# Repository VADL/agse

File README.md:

# agse
Autonomous Ground Support Equipment (AGSE) robot for the Vanderbilt Aerospace Design Lab (VADL)

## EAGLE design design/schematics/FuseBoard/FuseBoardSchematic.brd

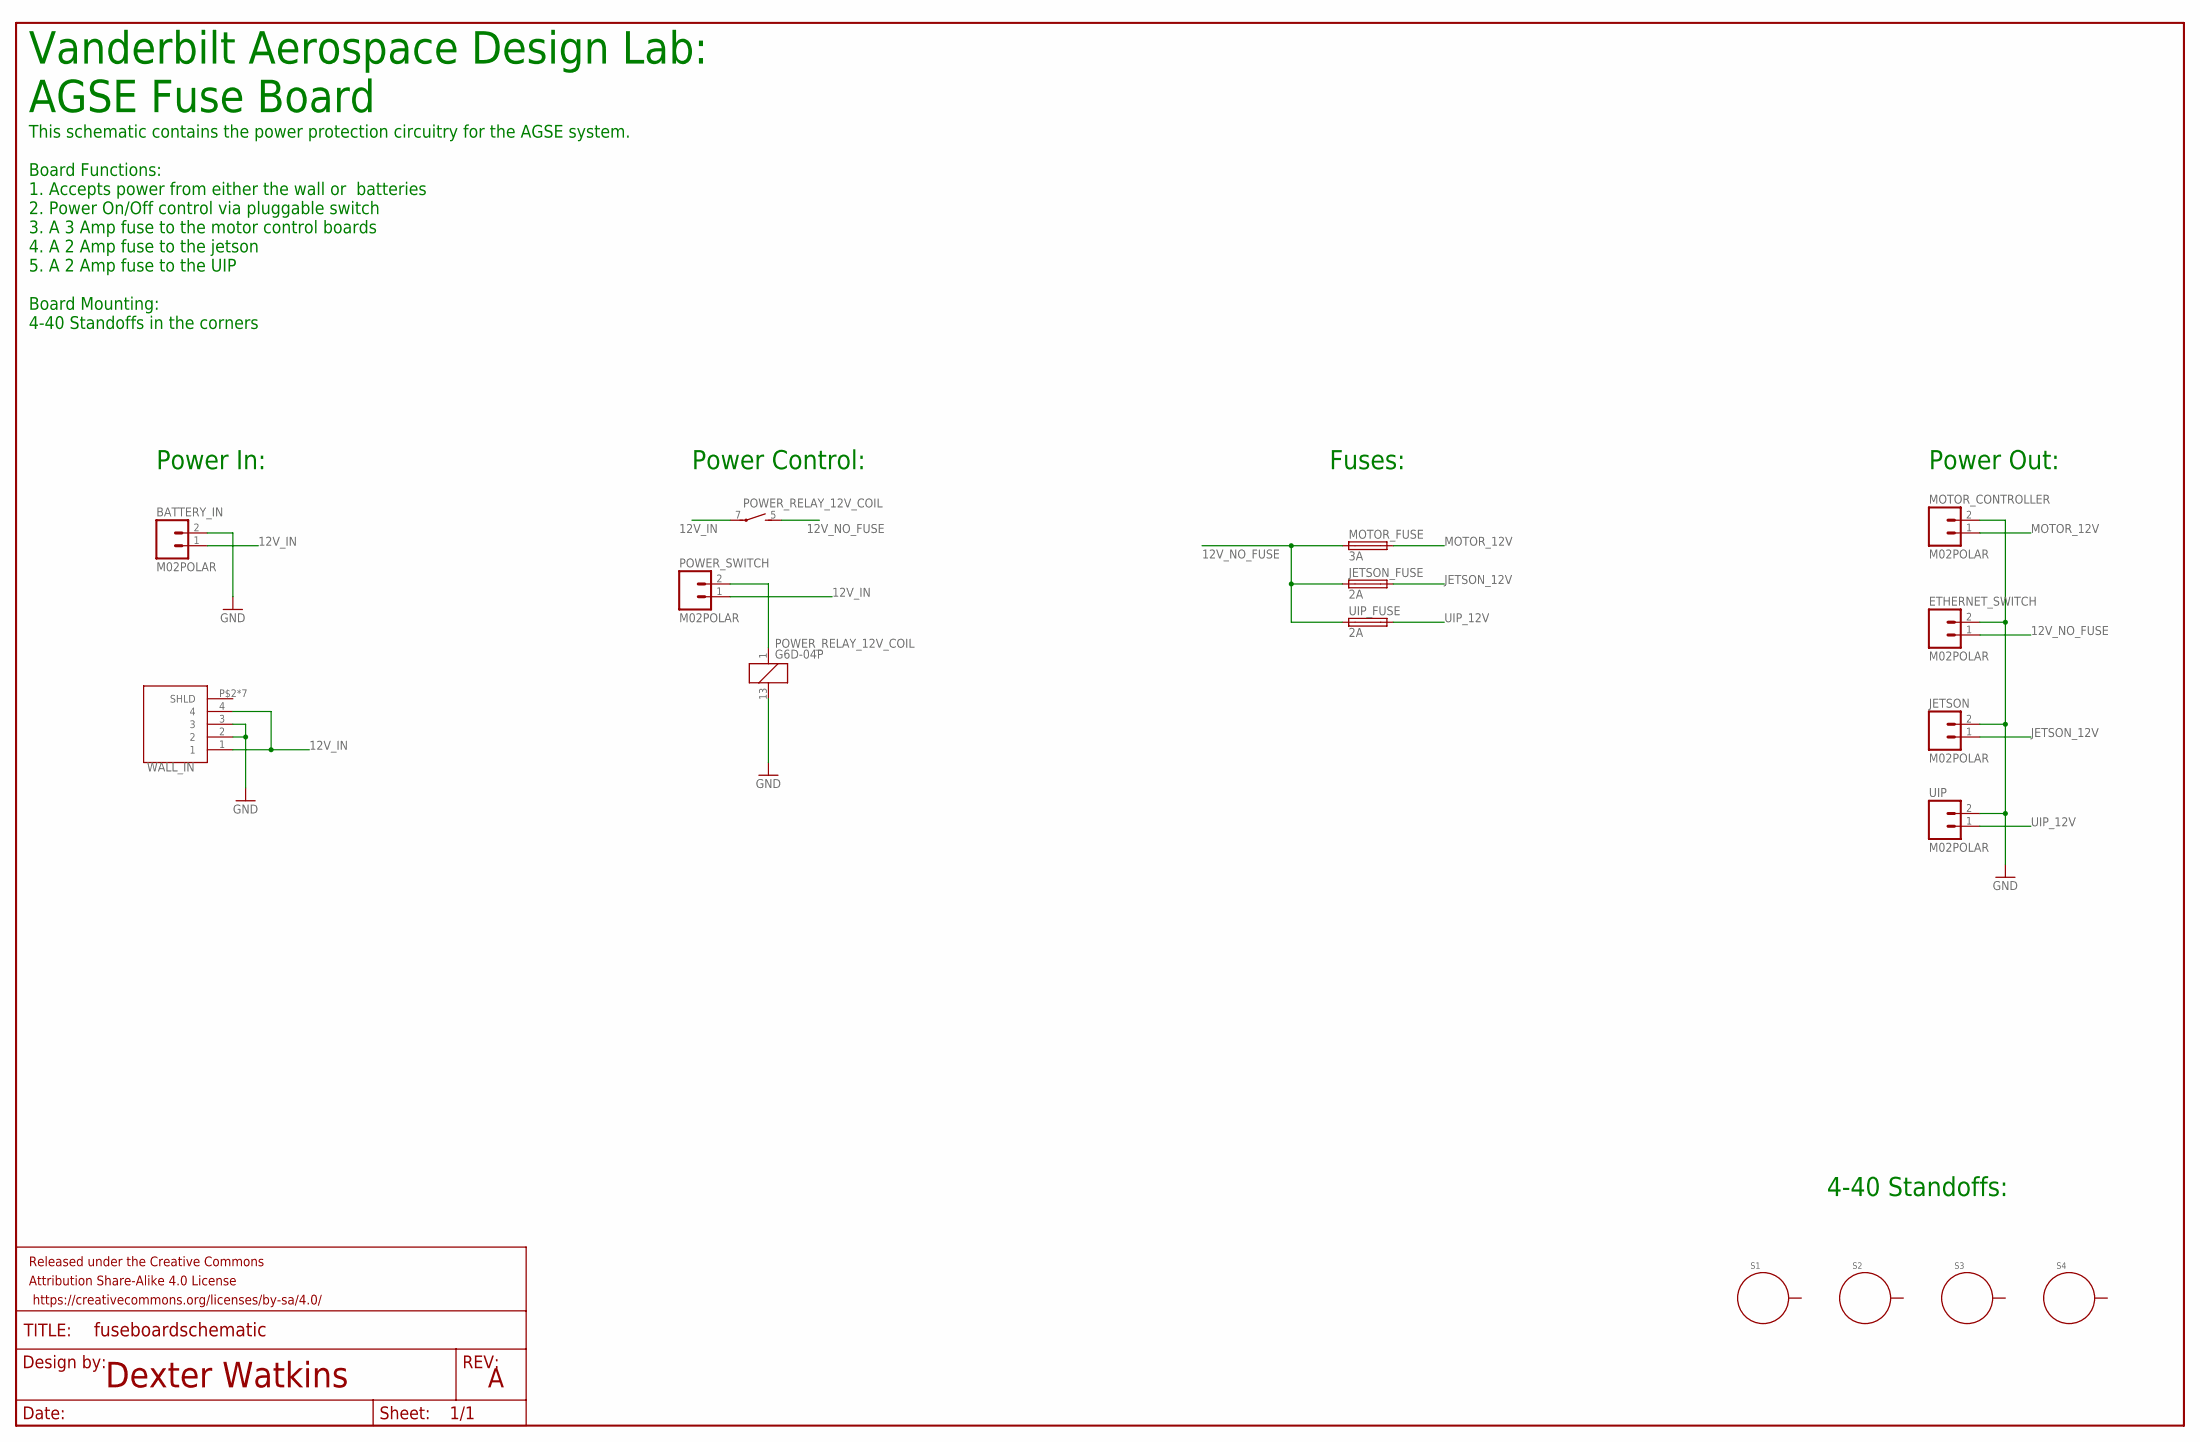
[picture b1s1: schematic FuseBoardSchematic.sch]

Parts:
BATTERY_IN: M02POLAR; MOLEX-1X2
ETHERNET_SWITCH: M02POLAR; MOLEX-1X2
FRAME1: FRAME-LEDGER; CREATIVE_COMMONS
JETSON: M02POLAR; MOLEX-1X2
JETSON_FUSE: 2A; SH22,5A
MOTOR_CONTROLLER: M02POLAR; MOLEX-1X2
MOTOR_FUSE: 3A; SH22,5A
POWER_RELAY_12V_COIL: G6D-04P; G6D-SOCKET
POWER_SWITCH: M02POLAR; MOLEX-1X2
S1, S2, S3, S4: STANDOFF_ELECTRICAL; STANDOFF-ELECTRICAL
UIP: M02POLAR; MOLEX-1X2
UIP_FUSE: 2A; SH22,5A
WALL_IN: KPJX-4S-S

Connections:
12V_IN: BATTERY_IN.1, POWER_RELAY_12V_COIL.7, POWER_SWITCH.1, WALL_IN.1, WALL_IN.4
12V_NO_FUSE: ETHERNET_SWITCH.1, JETSON_FUSE.1, MOTOR_FUSE.1, POWER_RELAY_12V_COIL.5 (S), UIP_FUSE.1
GND: BATTERY_IN.2, ETHERNET_SWITCH.2, JETSON.2, MOTOR_CONTROLLER.2, POWER_RELAY_12V_COIL.13 (2), UIP.2, WALL_IN.2, WALL_IN.3
JETSON_12V: JETSON.1, JETSON_FUSE.2
MOTOR_12V: MOTOR_CONTROLLER.1, MOTOR_FUSE.2
unnamed: POWER_RELAY_12V_COIL.1, POWER_SWITCH.2
UIP_12V: UIP.1, UIP_FUSE.2

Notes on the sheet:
Dexter Watkins
Vanderbilt Aerospace Design Lab: AGSE Fuse Board
This schematic contains the power protection circuitry for the AGSE system. Board Functions: 1. Accepts power from either the wall or batteries 2. Power On/Off control via pluggable switch 3. A 3 Amp fuse to the motor control boards 4. A 2 Amp fuse to the jetson 5. A 2 Amp fuse to the UIP Board Mou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
Power In:
Power Out:
Power Control:
Fuses:
4-40 Standoffs:

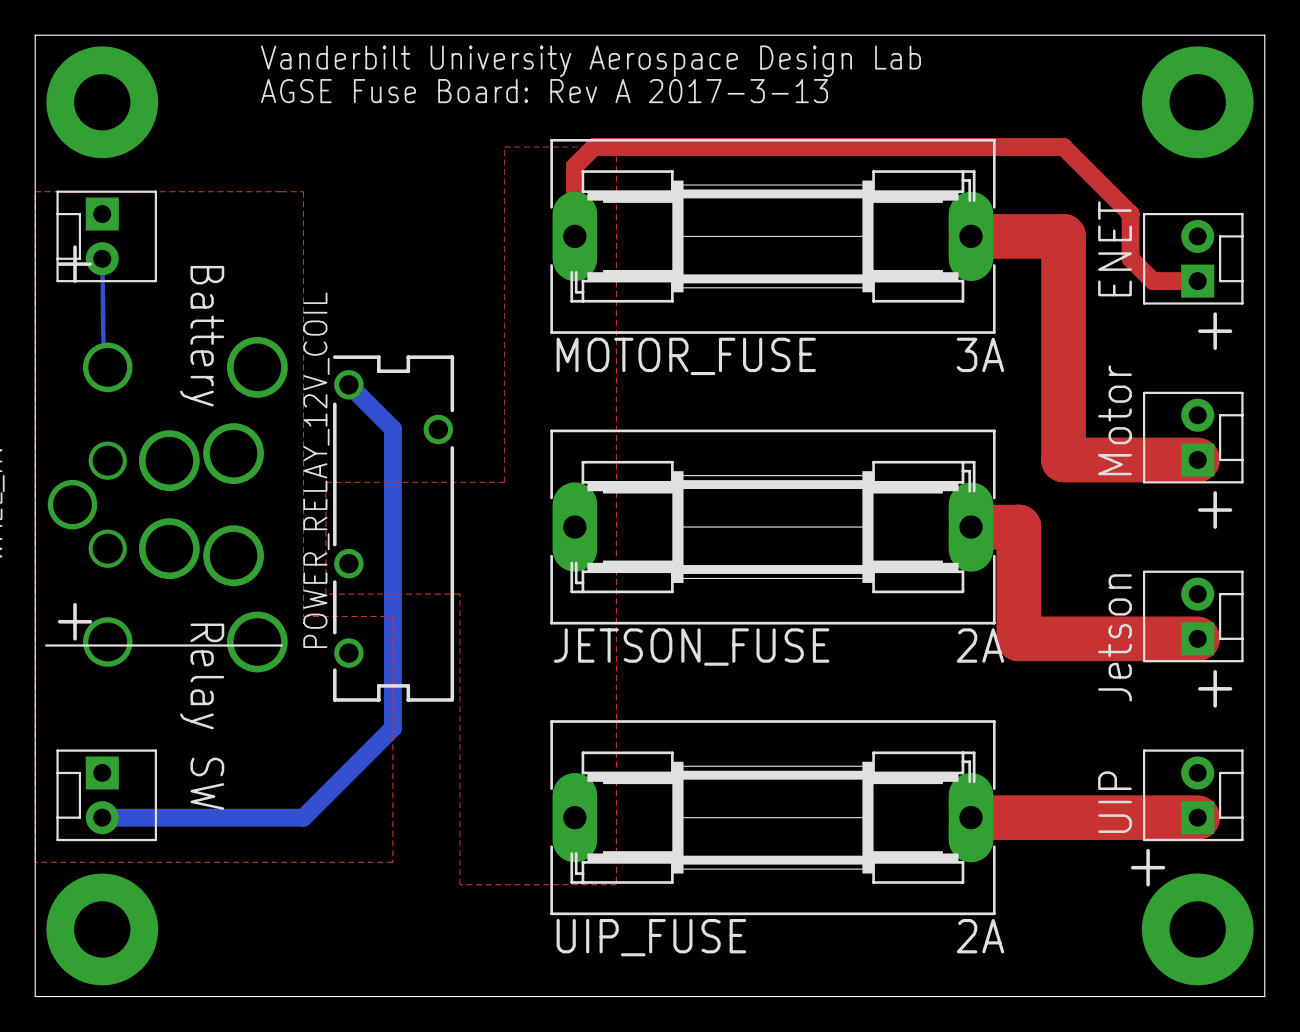
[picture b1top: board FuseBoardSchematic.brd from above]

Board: 2 copper layers, 69.8 x 54.6 mm, 16 parts (0 on the bottom side), 7 nets.

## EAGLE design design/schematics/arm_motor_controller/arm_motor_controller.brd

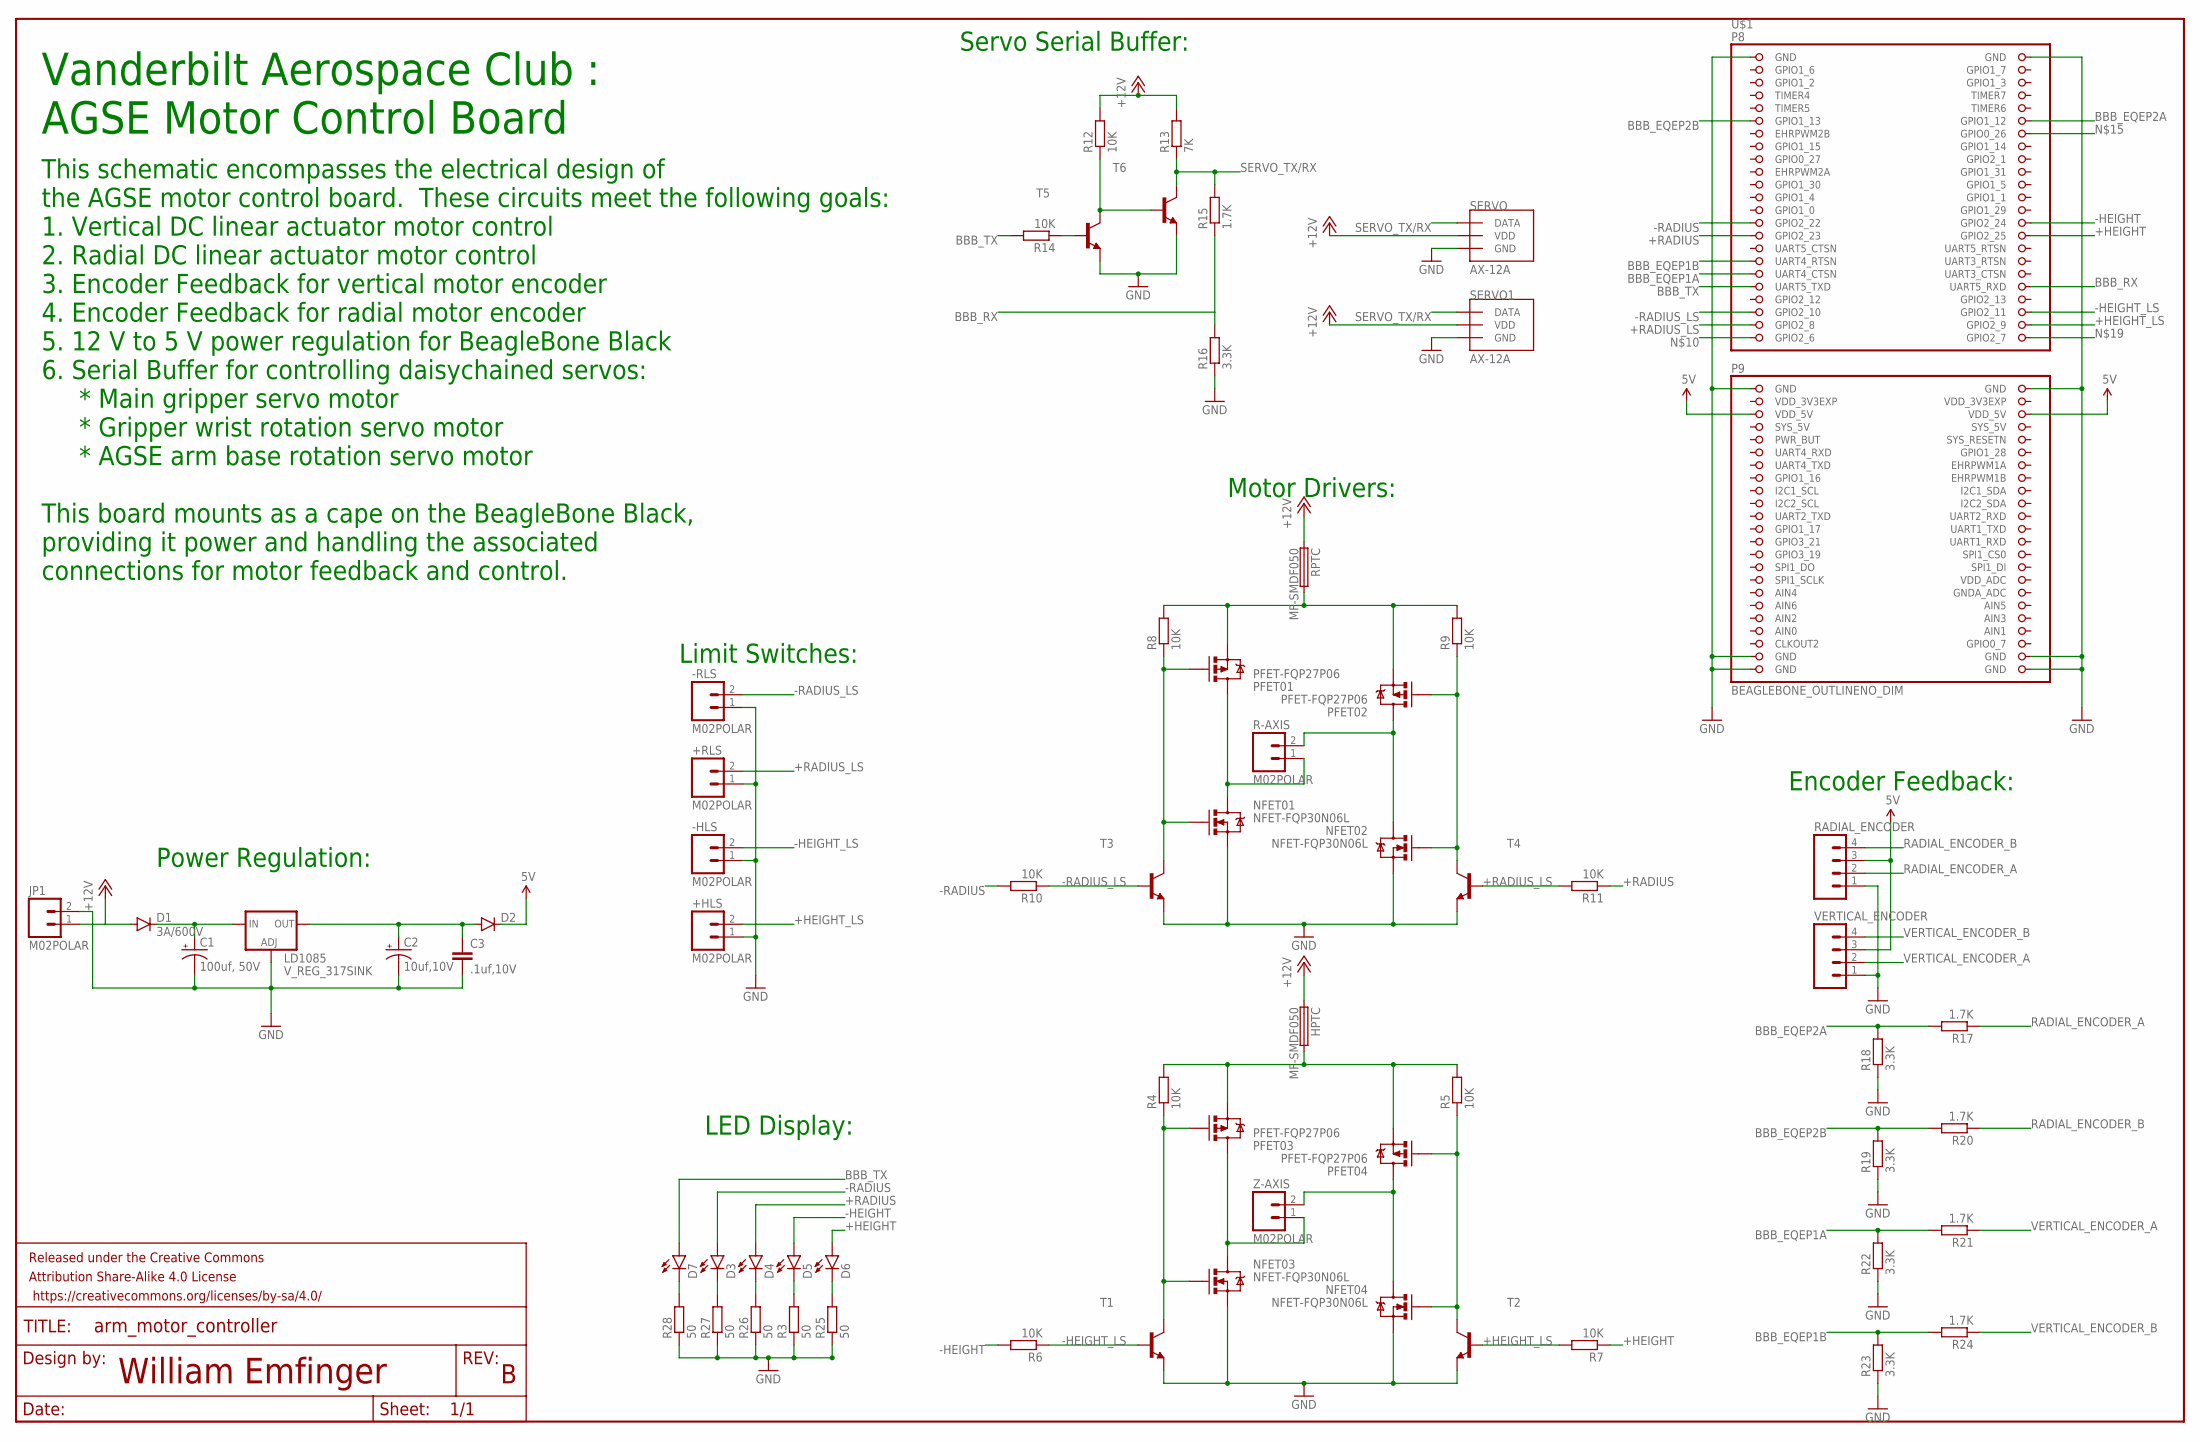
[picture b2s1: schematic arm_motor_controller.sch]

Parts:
+HLS: M02POLAR; MOLEX-1X2
+RLS: M02POLAR; MOLEX-1X2
-HLS: M02POLAR; MOLEX-1X2
-RLS: M02POLAR; MOLEX-1X2
C1: 100uf, 50V; PANASONIC_D
C2: 10uf,10V; EIA3216
C3: .1uf,10V; 0402-CAP
D1: 3A/600V; SMC
D2: DIODE1N4148; DIODE-1N4148
D3, D4, D5, D6, D7: LED-FKIT-1206; FKIT-LED-1206
FRAME1: FRAME-LEDGER; CREATIVE_COMMONS
HPTC: MF-SMDF050
JP1: M02POLAR; MOLEX-1X2
LD1085: V_REG_317SINK; TO220-ADJ
NFET01, NFET02, NFET03, NFET04: NFET-FQP30N06L; TO220V
PFET01, PFET02, PFET03, PFET04: PFET-FQP27P06; TO220V
R3, R25, R26, R27, R28: 50; M0805
R4, R5, R6, R7, R8, R9, R10, R11, R12, R14: 10K; M0805
R13: 7K; M0805
R15, R17, R20, R21, R24: 1.7K; M0805
R16, R18, R19, R22, R23: 3.3K; M0805
R-AXIS: M02POLAR; MOLEX-1X2
RADIAL_ENCODER: M04POLAR; MOLEX-1X4
RPTC: MF-SMDF050
SERVO, SERVO1: AX-12A; SPOX-3
T1, T2, T3, T4, T5, T6: BF820-NPN-SOT23-BEC; SOT23-BEC
U$1: BEAGLEBONE_OUTLINENO_DIM; BEAGLEBONE_SHIELD
VERTICAL_ENCODER: M04POLAR; MOLEX-1X4
Z-AXIS: M02POLAR; MOLEX-1X2

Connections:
5V: D2.C, RADIAL_ENCODER.3, U$1.51 (VDD_5V), U$1.52 (VDD_5V), VERTICAL_ENCODER.3
+12V: D1.A, HPTC.1, JP1.1, R12.2, R13.2, RPTC.1, SERVO.P$2 (VDD), SERVO1.P$2 (VDD)
+HEIGHT: D6.A, R7.1, U$1.30 (GPIO2_25)
+HEIGHT_LS: +HLS.2, R7.2, T2.B, U$1.44 (GPIO2_9)
+RADIUS: D4.A, R11.1, U$1.29 (GPIO2_23)
+RADIUS_LS: +RLS.2, R11.2, T4.B, U$1.43 (GPIO2_8)
-HEIGHT: D5.A, R6.2, U$1.28 (GPIO2_24)
-HEIGHT_LS: -HLS.2, R6.1, T1.B, U$1.42 (GPIO2_11)
-RADIUS: D3.A, R10.2, U$1.27 (GPIO2_22)
-RADIUS_LS: -RLS.2, R10.1, T3.B, U$1.41 (GPIO2_10)
AIN0: U$1.85 (AIN0)
BBB_EQEP1A: R21.2, R22.2, U$1.35 (UART4_CTSN)
BBB_EQEP1B: R23.2, R24.2, U$1.33 (UART4_RTSN)
BBB_EQEP2A: R17.2, R18.2, U$1.12 (GPIO1_12)
BBB_EQEP2B: R19.2, R20.2, U$1.11 (GPIO1_13)
BBB_RX: R15.1, R16.2, U$1.38 (UART5_RXD)
BBB_TX: D7.A, R14.2, U$1.37 (UART5_TXD)
GND: +HLS.1, +RLS.1, -HLS.1, -RLS.1, C1.-, C2.C (-), C3.2, JP1.2, LD1085.ADJ, NFET01.3 (S), NFET02.3 (S), NFET03.3 (S), NFET04.3 (S), R3.1, R16.1, R18.1, R19.1, R22.1, R23.1, R25.1, R26.1, R27.1, R28.1, RADIAL_ENCODER.1, SERVO.P$3 (GND), SERVO1.P$3 (GND), T1.E, T2.E, T3.E, T4.E, T5.E, T6.E, U$1.1 (GND), U$1.2 (GND), U$1.47 (GND), U$1.48 (GND), U$1.89 (GND), U$1.90 (GND), U$1.91 (GND), U$1.92 (GND), VERTICAL_ENCODER.1
H_VDD: HPTC.2, PFET03.3 (S), PFET04.3 (S), R4.2, R5.2
unnamed: D3.C, R27.2
unnamed: D4.C, R26.2
unnamed: C1.+, D1.C, LD1085.IN
unnamed: D5.C, R3.2
unnamed: D6.C, R25.2
unnamed: NFET03.1 (G), PFET03.1 (G), R4.1, T1.C
unnamed: NFET04.1 (G), PFET04.1 (G), R5.1, T2.C
unnamed: D7.C, R28.2
unnamed: NFET01.1 (G), PFET01.1 (G), R8.1, T3.C
unnamed: NFET02.1 (G), PFET02.1 (G), R9.1, T4.C
unnamed: R14.1, T5.B
unnamed: R12.1, T5.C, T6.B
R+: NFET01.2 (D), PFET01.2 (D), R-AXIS.1
R-: NFET02.2 (D), PFET02.2 (D), R-AXIS.2
RADIAL_ENCODER_A: R17.1, RADIAL_ENCODER.2
RADIAL_ENCODER_B: R20.1, RADIAL_ENCODER.4
R_VDD: PFET01.3 (S), PFET02.3 (S), R8.2, R9.2, RPTC.2
SERVO_TX/RX: R13.1, R15.2, SERVO.P$1 (DATA), SERVO1.P$1 (DATA), T6.C
SYS_5V: U$1.53 (SYS_5V)
VDD_3V3EXP: U$1.49 (VDD_3V3EXP), U$1.50 (VDD_3V3EXP)
VERTICAL_ENCODER_A: R21.1, VERTICAL_ENCODER.2
VERTICAL_ENCODER_B: R24.1, VERTICAL_ENCODER.4
VOUT: C2.A (+), C3.1, D2.A, LD1085.OUT
Z+: NFET03.2 (D), PFET03.2 (D), Z-AXIS.1
Z-: NFET04.2 (D), PFET04.2 (D), Z-AXIS.2

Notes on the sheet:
Vanderbilt Aerospace Club : AGSE Motor Control Board
This schematic encompasses the electrical design of the AGSE motor control board. These circuits meet the following goals: 1. Vertical DC linear actuator motor control 2. Radial DC linear actuator motor control 3. Encoder Feedback for vertical motor encoder 4. Encoder Feedback for radial motor enco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
William Emfinger
Power Regulation:
Limit Switches:
Motor Drivers:
Servo Serial Buffer:
Encoder Feedback:
LED Display:

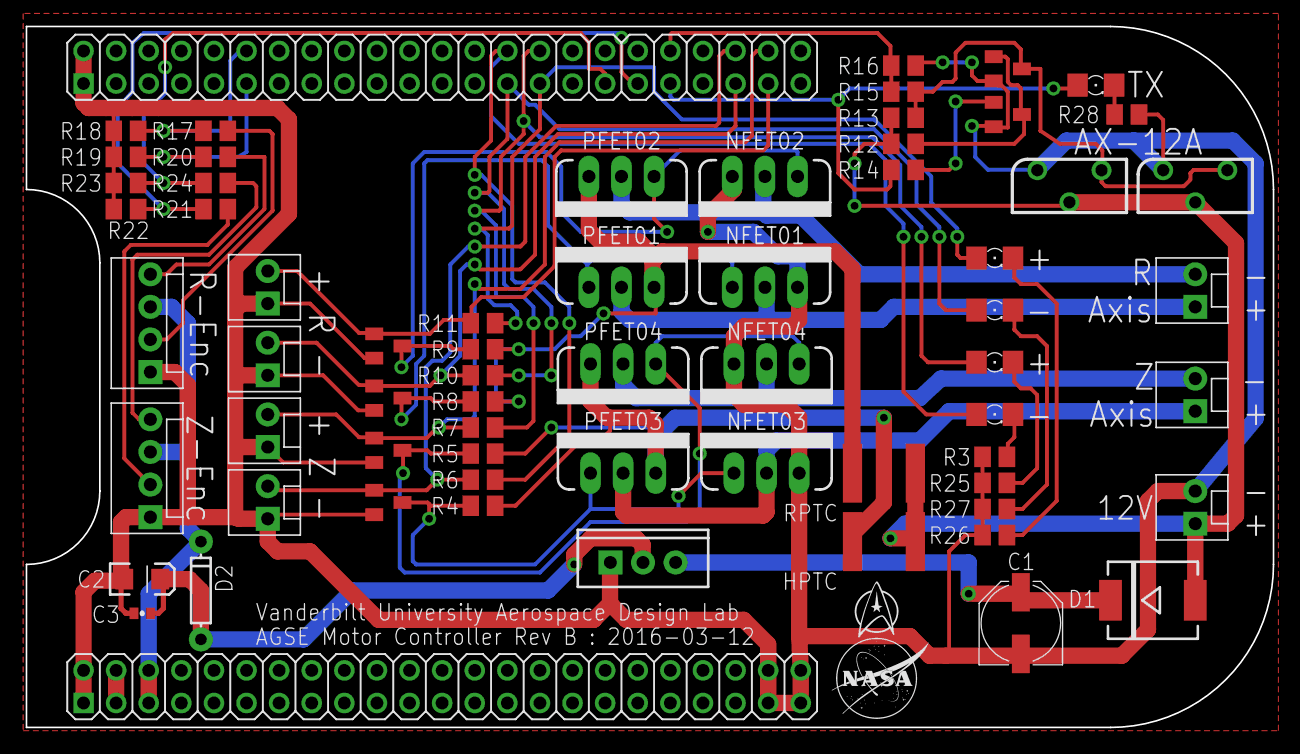
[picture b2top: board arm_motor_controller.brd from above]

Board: 2 copper layers, 97.2 x 54.6 mm, 67 parts (0 on the bottom side), 42 nets.

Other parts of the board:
DRILEGEND: DRILEGEND

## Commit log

2016-03-10 copied over relevant files from agse2015 repo
2016-03-10 updated adafruit library
    to have a version of the board which only shows the outline, but doesn't
    set the dimension layer. also added the adafruit library to the repo
    for use with other schematics.
2016-03-11 working on schematic/board.
2016-03-11 routed the board.
2016-03-12 working on updating the board routing.
2016-03-12 updated routes.
2016-03-12 Added Preliminary Fuse Board
2016-03-12 Added datasheets on limit switch and relay
2016-03-12 finalizing motor control board.
2016-03-12 finalizing motor controller.
2016-03-12 updated boards and BoM. added PTCs, changed to molex connectors, and updated diode and other componenets.
2016-03-13 Conglomerated BOM into a single spreadsheet
2016-03-13 Routed Fuse Board
2016-03-13 Removed clutter
2016-03-13 Updated BOM
2016-03-13 updated BoM with motor control info.
2016-03-14 Fixed routing issues and updated BOM
2016-03-14 Updated fuse ratings
2016-03-14 added KPJX connector library.
2016-03-14 minor update so at least the library should work for drc and manufacture?
2016-03-14 added document layer and name/value
2016-03-14 Added wall power port to fuse board
2016-03-14 added fuses to bom
2016-03-14 updated gitignore
2016-03-15 Generated Gerber Files for Motor Controller and Fuse Board
2016-03-16 Added board dimensions
2016-03-17 Updated BOM with prices
2016-03-18 Optimized BOM Quantities for bulk pricing
2016-03-18 Added AGSE CAD (Solidworks)
2016-03-18 Updated CAD View Config
2016-03-18 BOM Tweaks
2016-03-20 Added Undercarriage CAD
2016-03-20 Added Placeholders for Jetson and Fuseboard on Tray
2016-03-20 Added Screenshots of CAD
2016-03-24 Added components to electrical assemble CAD
2016-03-27 added updated dts files and readme.
2016-03-29 Added Limit Switch Footprint
2017-05-30 added logs and images from last years test (found on old VM).

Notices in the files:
parts and their libraries:
SparkFun-Aesthetics: Licensing: Creative Commons ShareAlike 4.0 International - https://creativecommons.org/licenses/by-sa/4.0
SparkFun-Aesthetics: Released under the Creative Commons Attribution Share-Alike 4.0 License
SparkFun-Aesthetics: https://creativecommons.org/licenses/by-sa/4.0
